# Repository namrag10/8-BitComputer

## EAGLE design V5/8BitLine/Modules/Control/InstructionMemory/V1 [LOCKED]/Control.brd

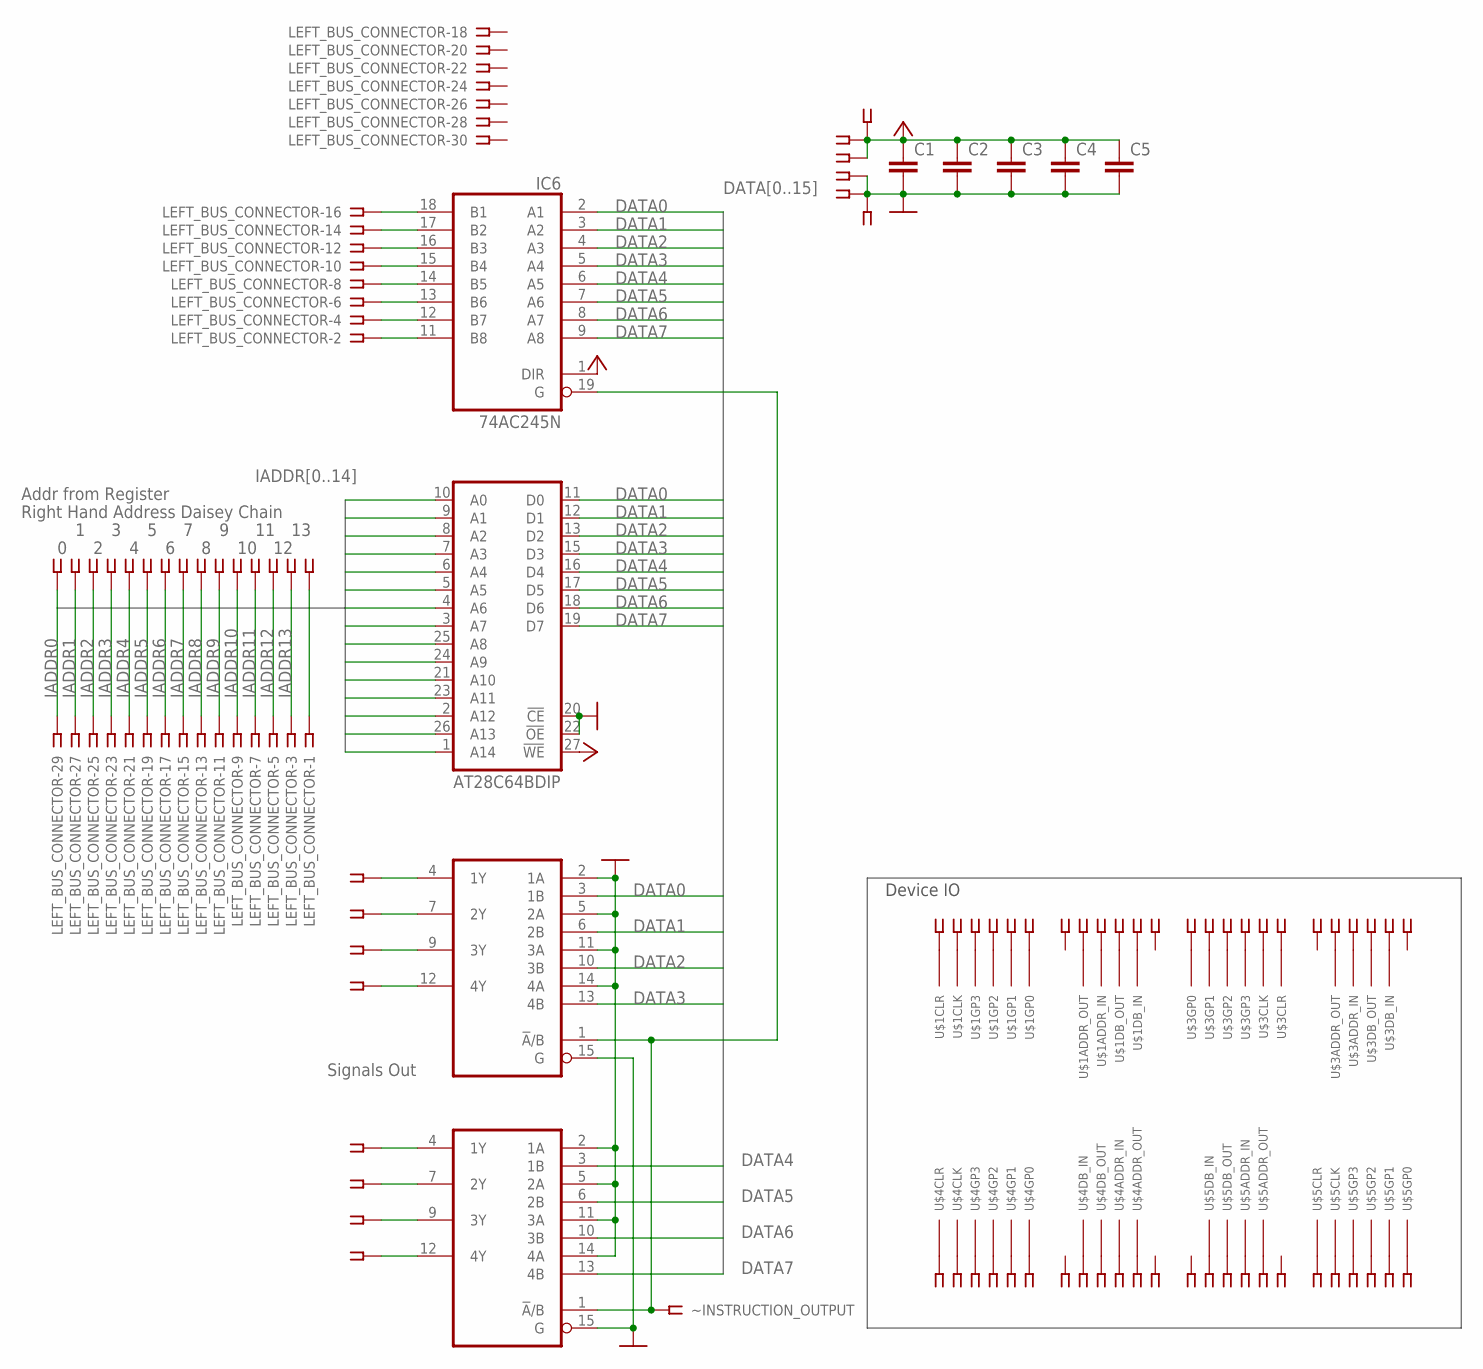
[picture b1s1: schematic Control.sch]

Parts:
C1, C2, C3, C4, C5: C2.5/2; C2.5-2
IC4, IC5: 74AC157N; DIL16
IC6: 74AC245N; DIL20
LEFT_BUS_CONNECTOR: SSW-115-02-G-D
MEZZANINE: SSW-104-02-G-S
U$1, U$3, U$4, U$5: CONTROL_SIG-INT; CONTROL_SIG-INT-FOOT
U$2: AT28C64BDIP; DIP28-WIDE
X1, X2, X3, X4, X6, X7, X8, X9: SSW-106-02-G-S
X5: SSW-108-02-G-S
X11: SSW-102-02-G-S
X12: SSW-115-02-G-S
~INSTRUCTION_OUTPUT: SSW-101-02-G-S

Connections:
DATA0: IC4.3 (1B), IC6.2 (A1), U$2.11 (D0)
DATA1: IC4.6 (2B), IC6.3 (A2), U$2.12 (D1)
DATA2: IC4.10 (3B), IC6.4 (A3), U$2.13 (D2)
DATA3: IC4.13 (4B), IC6.5 (A4), U$2.15 (D3)
DATA4: IC5.3 (1B), IC6.6 (A5), U$2.16 (D4)
DATA5: IC5.6 (2B), IC6.7 (A6), U$2.17 (D5)
DATA6: IC5.10 (3B), IC6.8 (A7), U$2.18 (D6)
DATA7: IC5.13 (4B), IC6.9 (A8), U$2.19 (D7)
GND: C1.2, C2.2, C3.2, C4.2, C5.2, IC4.2 (1A), IC4.5 (2A), IC4.8 (GND), IC4.11 (3A), IC4.14 (4A), IC4.15 (G), IC5.2 (1A), IC5.5 (2A), IC5.8 (GND), IC5.11 (3A), IC5.14 (4A), IC5.15 (G), IC6.10 (GND), MEZZANINE.3, MEZZANINE.4, U$1.GND, U$2.14 (GND), U$2.20 (!CE), U$2.22 (!OE), U$3.GND, U$4.GND, U$5.GND, X11.2
IADDR0: LEFT_BUS_CONNECTOR.29, U$2.10 (A0), X12.1
IADDR1: LEFT_BUS_CONNECTOR.27, U$2.9 (A1), X12.2
IADDR2: LEFT_BUS_CONNECTOR.25, U$2.8 (A2), X12.3
IADDR3: LEFT_BUS_CONNECTOR.23, U$2.7 (A3), X12.4
IADDR4: LEFT_BUS_CONNECTOR.21, U$2.6 (A4), X12.5
IADDR5: LEFT_BUS_CONNECTOR.19, U$2.5 (A5), X12.6
IADDR6: LEFT_BUS_CONNECTOR.17, U$2.4 (A6), X12.7
IADDR7: LEFT_BUS_CONNECTOR.15, U$2.3 (A7), X12.8
IADDR8: LEFT_BUS_CONNECTOR.13, U$2.25 (A8), X12.9
IADDR9: LEFT_BUS_CONNECTOR.11, U$2.24 (A9), X12.10
IADDR10: LEFT_BUS_CONNECTOR.9, U$2.21 (A10), X12.11
IADDR11: LEFT_BUS_CONNECTOR.7, U$2.23 (A11), X12.12
IADDR12: LEFT_BUS_CONNECTOR.5, U$2.2 (A12), X12.13
IADDR13: LEFT_BUS_CONNECTOR.3, U$2.26 (A13), X12.14
IADDR14: LEFT_BUS_CONNECTOR.1, U$2.1 (A14), X12.15
I_OUT: IC4.1 (!A!/B), IC5.1 (!A!/B), IC6.19 (G), ~INSTRUCTION_OUTPUT.1
unnamed: U$1.GP0 (0), X1.6
unnamed: U$1.GP1 (0), X1.5
unnamed: U$1.GP2 (0), X1.4
unnamed: U$1.GP3 (0), X1.3
unnamed: U$1.CLK (0), X1.2
unnamed: U$1.CLR (0), X1.1
unnamed: U$1.DB_IN (0), X2.2
unnamed: U$1.DB_OUT (0), X2.3
unnamed: U$1.ADDR_IN (0), X2.4
unnamed: U$1.ADDR_OT (0), X2.5
unnamed: U$3.GP0 (0), X3.6
unnamed: U$3.GP1 (0), X3.5
unnamed: U$3.GP2 (0), X3.4
unnamed: U$3.GP3 (0), X3.3
unnamed: U$3.CLK (0), X3.2
unnamed: U$3.CLR (0), X3.1
unnamed: U$3.DB_IN (0), X4.2
unnamed: U$3.DB_OUT (0), X4.3
unnamed: U$3.ADDR_IN (0), X4.4
unnamed: U$3.ADDR_OT (0), X4.5
unnamed: U$4.CLR (0), X9.1
unnamed: U$4.CLK (0), X9.2
unnamed: U$4.GP0 (0), X9.6
unnamed: U$4.GP1 (0), X9.5
unnamed: U$4.GP2 (0), X9.4
unnamed: U$4.GP3 (0), X9.3
unnamed: U$4.DB_IN (0), X8.2
unnamed: U$4.DB_OUT (0), X8.3
unnamed: U$4.ADDR_IN (0), X8.4
unnamed: U$4.ADDR_OT (0), X8.5
unnamed: U$5.GP0 (0), X6.6
unnamed: U$5.GP3 (0), X6.3
unnamed: U$5.GP2 (0), X6.4
unnamed: U$5.GP1 (0), X6.5
unnamed: U$5.CLK (0), X6.2
unnamed: U$5.CLR (0), X6.1
unnamed: U$5.DB_IN (0), X7.2
unnamed: U$5.DB_OUT (0), X7.3
unnamed: U$5.ADDR_IN (0), X7.4
unnamed: U$5.ADDR_OT (0), X7.5
O_DB0: IC6.18 (B1), LEFT_BUS_CONNECTOR.16
O_DB1: IC6.17 (B2), LEFT_BUS_CONNECTOR.14
O_DB2: IC6.16 (B3), LEFT_BUS_CONNECTOR.12
O_DB3: IC6.15 (B4), LEFT_BUS_CONNECTOR.10
O_DB4: IC6.14 (B5), LEFT_BUS_CONNECTOR.8
O_DB5: IC6.13 (B6), LEFT_BUS_CONNECTOR.6
O_DB6: IC6.12 (B7), LEFT_BUS_CONNECTOR.4
O_DB7: IC6.11 (B8), LEFT_BUS_CONNECTOR.2
SIG_1: IC4.4 (1Y), X5.1
SIG_2: IC4.7 (2Y), X5.2
SIG_3: IC4.9 (3Y), X5.3
SIG_4: IC4.12 (4Y), X5.4
SIG_5: IC5.4 (1Y), X5.5
SIG_6: IC5.7 (2Y), X5.6
SIG_7: IC5.9 (3Y), X5.7
SIG_8: IC5.12 (4Y), X5.8
VCC: C1.1, C2.1, C3.1, C4.1, C5.1, IC4.16 (VCC), IC5.16 (VCC), IC6.1 (DIR), IC6.20 (VCC), MEZZANINE.1, MEZZANINE.2, U$1.VCC, U$2.27 (!WE), U$2.28 (VCC), U$3.VCC, U$4.VCC, U$5.VCC, X11.1

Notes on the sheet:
Device IO
Signals Out
Right Hand Address Daisey Chain
Addr from Register

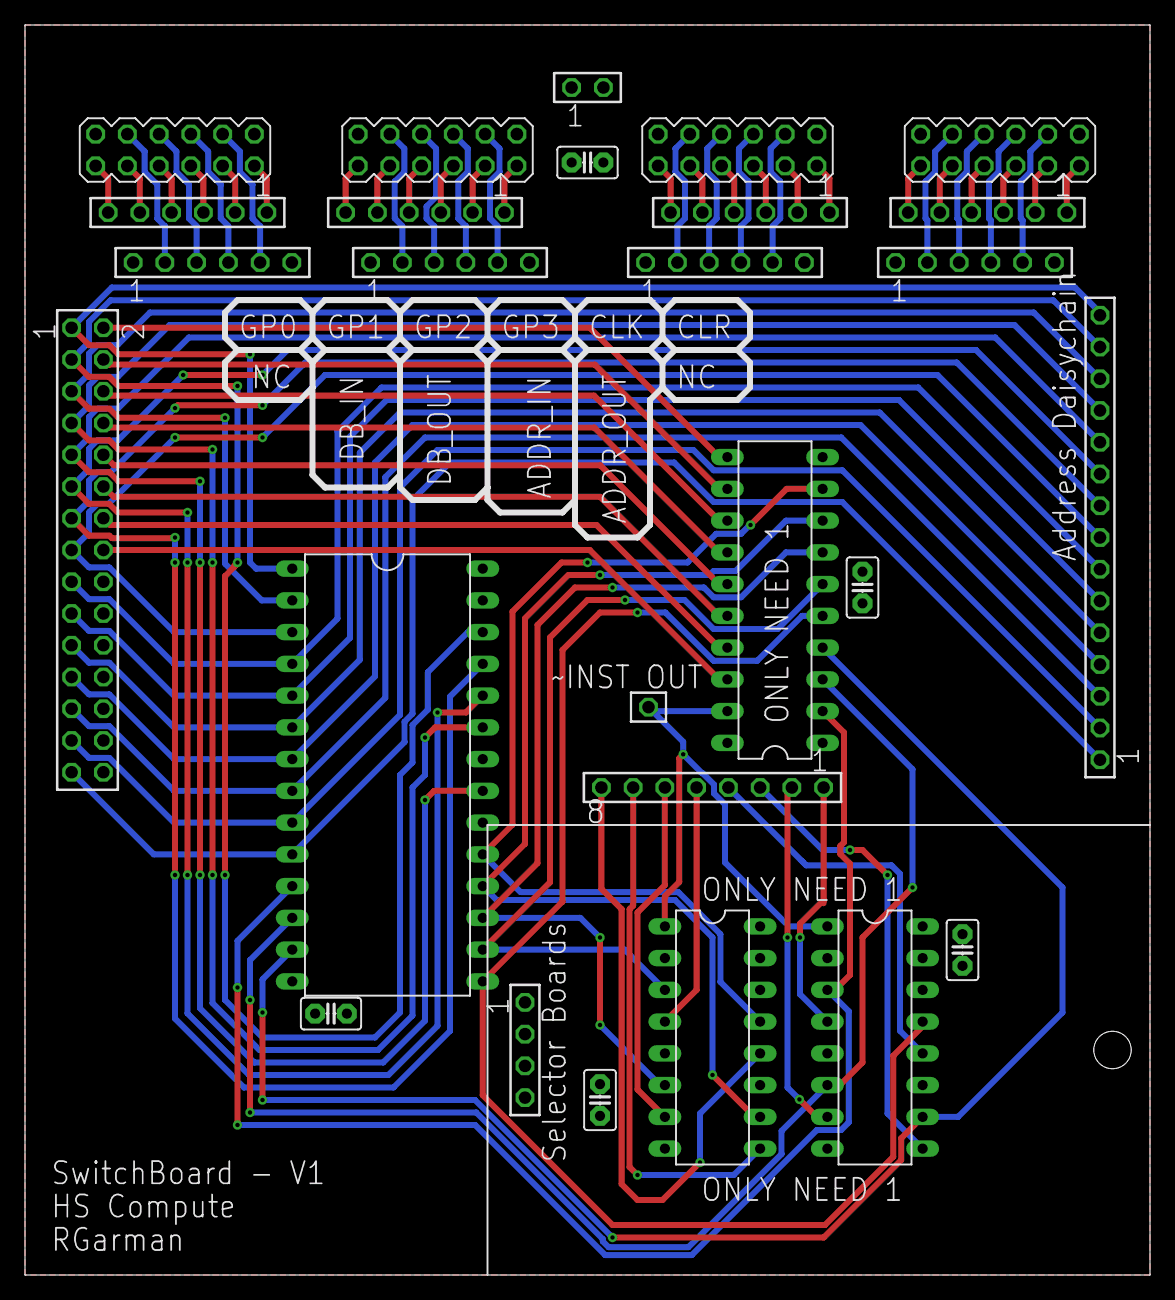
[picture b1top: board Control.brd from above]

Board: 2 copper layers, 90.0 x 100.0 mm, 27 parts (0 on the bottom side), 82 nets.

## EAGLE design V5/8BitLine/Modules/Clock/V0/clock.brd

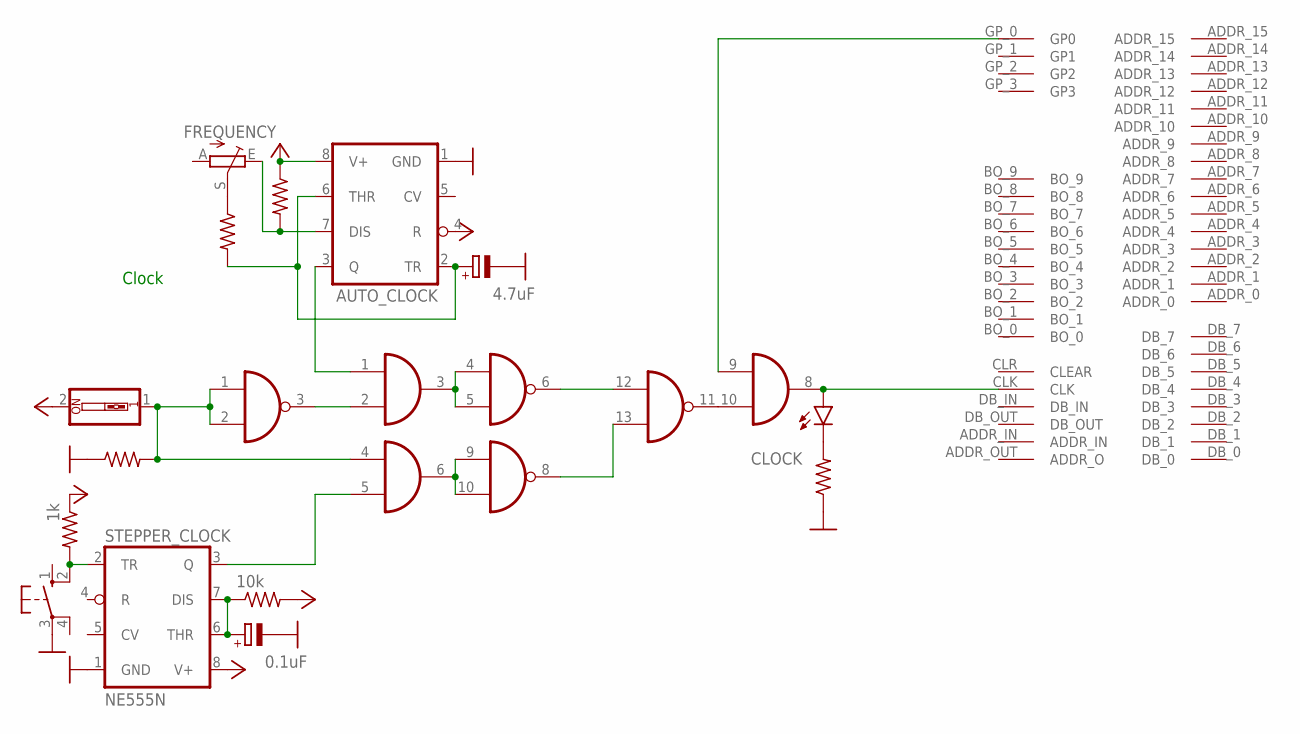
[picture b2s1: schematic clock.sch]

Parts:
AND_GATE_: 74LS08N; DIL14
AUTO_CLOCK: NE555N; DIL08
C1: 4.7uF; E2-5
C2: 0.1uF; E2-5
CLK_MODE: SWITCH; EDG-01
CLK_TRIGGER: SWITCH; B3F-10XX
CLOCK: Yellow; LED5MM
FREQUENCY: 100k; RJ9W
NAND: 74ACT00N; DIL14
R1, R2: 1k; 0204/7
R3: 10k; 0204/7
R4, R6: 220; 0204/7
R5: ~220; 0204/7
STEPPER_CLOCK: NE555N; DIL08
U$1: BACKPLATE_INTERFACEEDGE_FINGER; BACK_INTERFACE-FOOT

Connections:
CLOCK: AND_GATE_.8 (O), CLOCK.A, U$1.CLK
GND: AND_GATE_.7 (GND), AUTO_CLOCK.1 (GND), C1.-, C2.-, CLK_TRIGGER.3, NAND.7 (GND), R4.1, R5.1, STEPPER_CLOCK.1 (GND), U$1.GND_0 (GND), U$1.GND_1 (GND)
HLT: AND_GATE_.9 (I0), U$1.GP_0 (GP0)
MODE_SIGNAL: AND_GATE_.4 (I0), CLK_MODE.1, NAND.1 (I0), NAND.2 (I1), R4.2
unnamed: C2.+, R3.1, STEPPER_CLOCK.6 (THR), STEPPER_CLOCK.7 (DIS)
unnamed: CLK_TRIGGER.2 (S1), R2.2, STEPPER_CLOCK.2 (TR)
unnamed: CLOCK.K (C), R5.2
unnamed: AND_GATE_.5 (I1), STEPPER_CLOCK.3 (Q)
unnamed: AND_GATE_.3 (O), NAND.4 (I0), NAND.5 (I1)
unnamed: AND_GATE_.1 (I0), AUTO_CLOCK.3 (Q)
unnamed: AND_GATE_.6 (O), NAND.9 (I0), NAND.10 (I1)
unnamed: NAND.8 (O), NAND.13 (I1)
unnamed: AND_GATE_.2 (I1), NAND.3 (O)
unnamed: NAND.6 (O), NAND.12 (I0)
unnamed: AND_GATE_.10 (I1), NAND.11 (O)
unnamed: AUTO_CLOCK.2 (TR), AUTO_CLOCK.6 (THR), C1.+, R6.2
unnamed: FREQUENCY.S, R6.1
unnamed: AUTO_CLOCK.7 (DIS), FREQUENCY.E, R1.2
VCC: AND_GATE_.14 (VCC), AUTO_CLOCK.4 (R), AUTO_CLOCK.8 (V+), CLK_MODE.2, NAND.14 (VCC), R1.1, R2.1, R3.2, STEPPER_CLOCK.8 (V+), U$1.VCC_0 (VCC), U$1.VCC_1 (VCC)

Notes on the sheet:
Clock

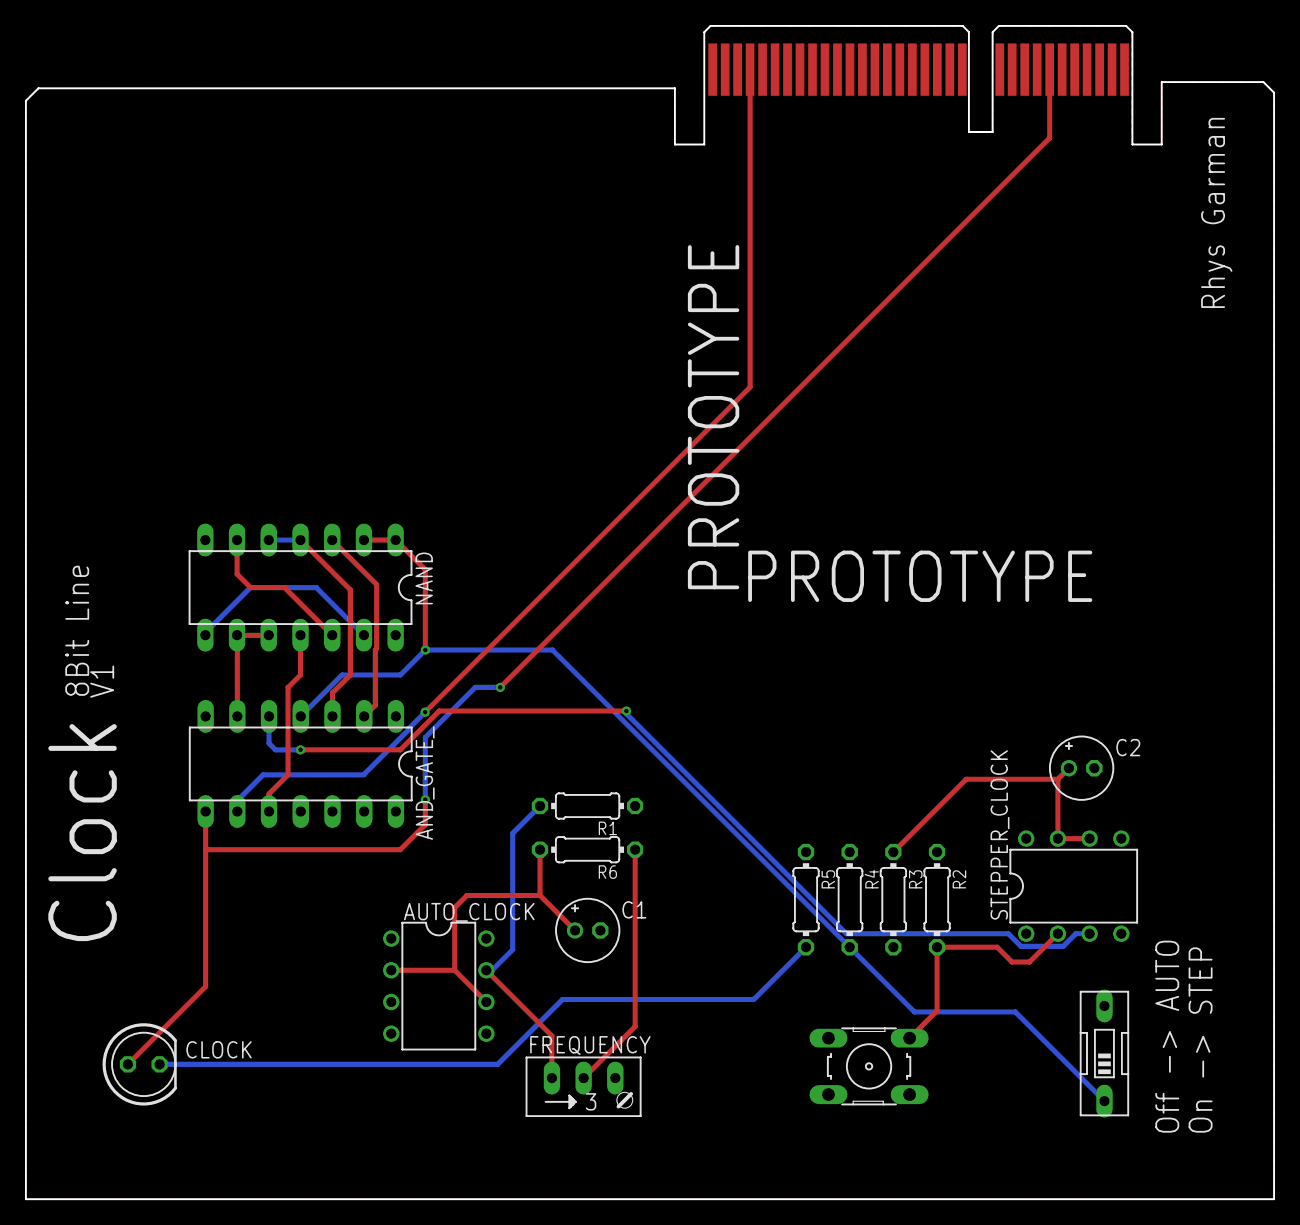
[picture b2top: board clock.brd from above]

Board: 2 copper layers, 100.0 x 94.0 mm, 17 parts (0 on the bottom side), 19 nets.

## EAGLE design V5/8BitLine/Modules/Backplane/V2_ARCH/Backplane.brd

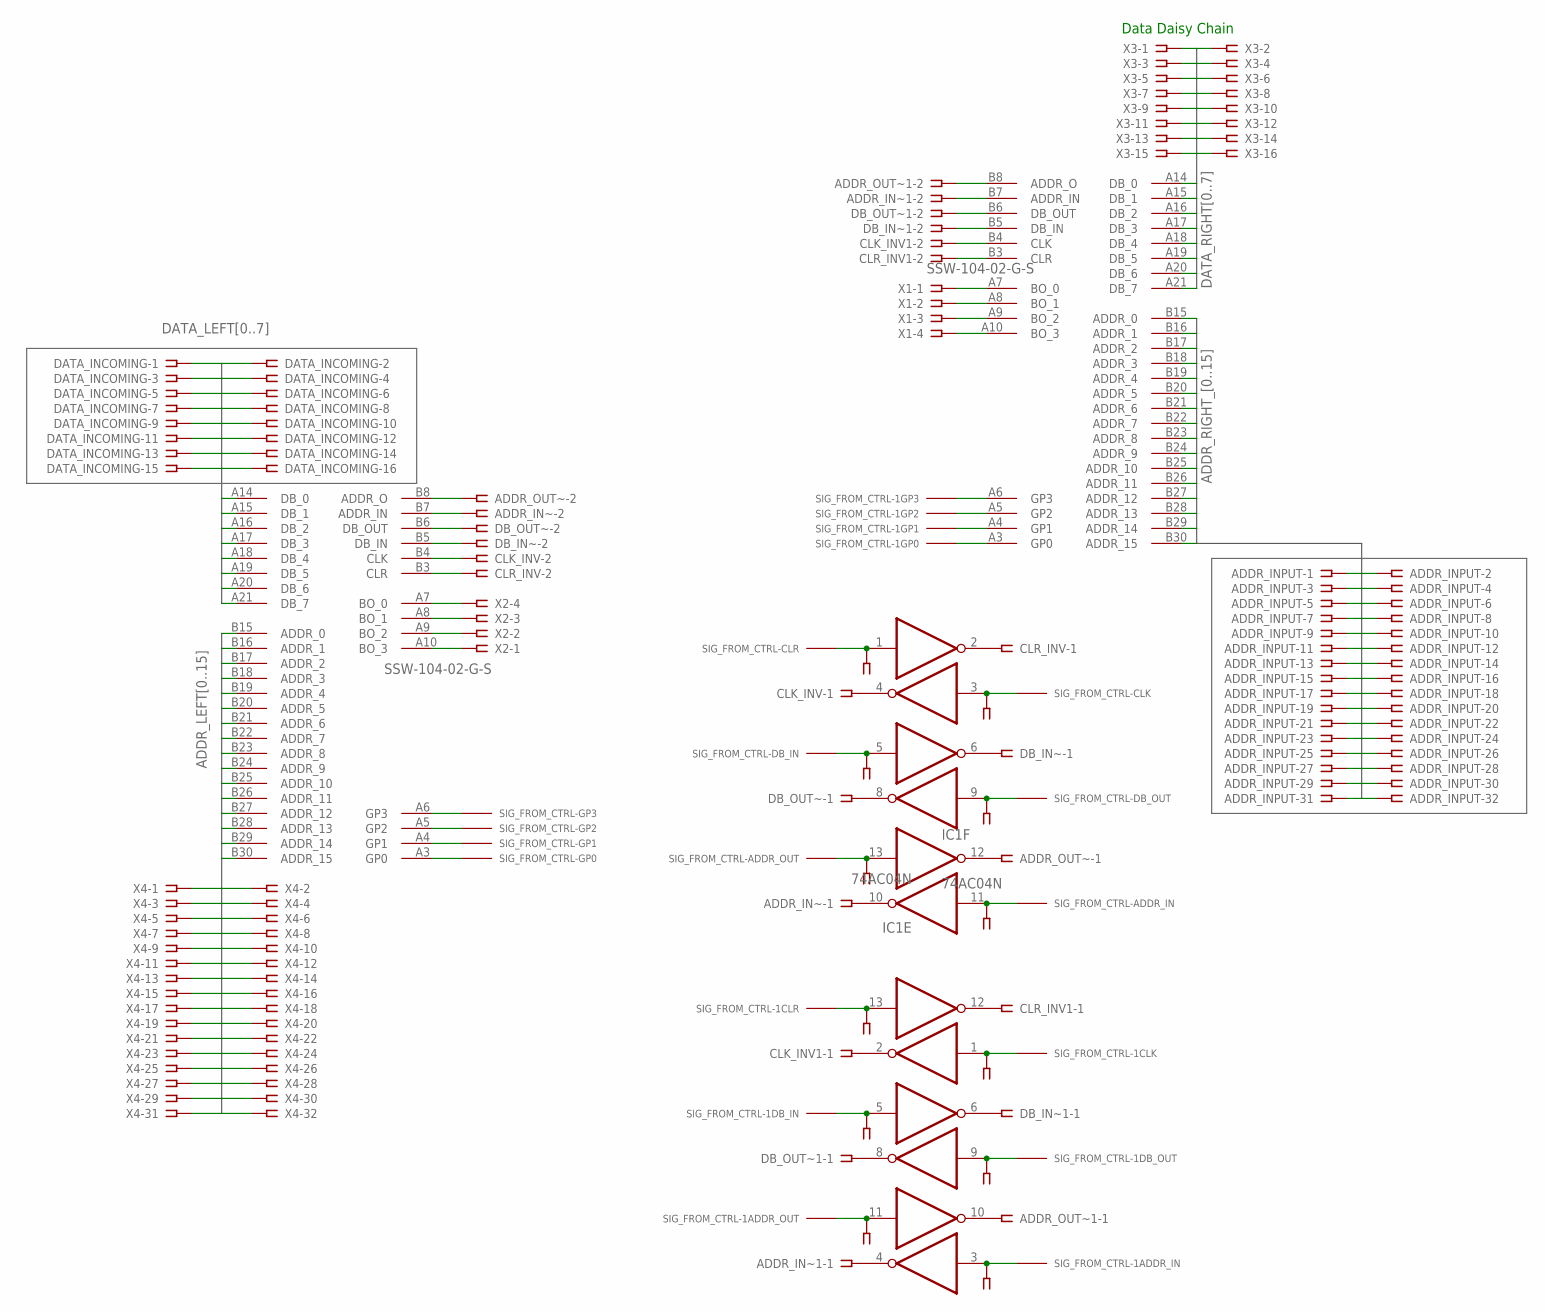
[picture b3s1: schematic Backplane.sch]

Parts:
ADDR_INPUT: SSW-116-02-G-D
ADDR_IN~, ADDR_IN~1: SSW-103-02-G-S
ADDR_OUT~, ADDR_OUT~1: SSW-103-02-G-S
CLK_INV, CLK_INV1: SSW-103-02-G-S
CLR_INV, CLR_INV1: SSW-103-02-G-S
DATA_INCOMING: SSW-108-02-G-D
DB_IN~, DB_IN~1: SSW-103-02-G-S
DB_OUT~, DB_OUT~1: SSW-103-02-G-S
IC1, IC2: 74AC04N; DIL14
SIG_FROM_CTRL-, SIG_FROM_CTRL-1: CONTROL_SIG-INT; CONTROL_SIG-INT-FOOT
U$1, U$2: BACKPLATE_INTERFACEHEADER; PCI_INTERFACE
X1, X2: SSW-104-02-G-S
X3: SSW-108-02-G-D
X4: SSW-116-02-G-D

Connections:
ADDR_IN: ADDR_IN~1.2, U$1.B7 (ADDR_IN)
ADDR_LEFT0: U$2.B15 (ADDR_0), X4.1, X4.2
ADDR_LEFT1: U$2.B16 (ADDR_1), X4.3, X4.4
ADDR_LEFT2: U$2.B17 (ADDR_2), X4.5, X4.6
ADDR_LEFT3: U$2.B18 (ADDR_3), X4.7, X4.8
ADDR_LEFT4: U$2.B19 (ADDR_4), X4.9, X4.10
ADDR_LEFT5: U$2.B20 (ADDR_5), X4.11, X4.12
ADDR_LEFT6: U$2.B21 (ADDR_6), X4.13, X4.14
ADDR_LEFT7: U$2.B22 (ADDR_7), X4.15, X4.16
ADDR_LEFT8: U$2.B23 (ADDR_8), X4.17, X4.18
ADDR_LEFT9: U$2.B24 (ADDR_9), X4.19, X4.20
ADDR_LEFT10: U$2.B25 (ADDR_10), X4.21, X4.22
ADDR_LEFT11: U$2.B26 (ADDR_11), X4.23, X4.24
ADDR_LEFT12: U$2.B27 (ADDR_12), X4.25, X4.26
ADDR_LEFT13: U$2.B28 (ADDR_13), X4.27, X4.28
ADDR_LEFT14: U$2.B29 (ADDR_14), X4.29, X4.30
ADDR_LEFT15: U$2.B30 (ADDR_15), X4.31, X4.32
ADDR_OUT: ADDR_OUT~1.2, U$1.B8 (ADDR_O)
ADDR_RIGHT_0: ADDR_INPUT.1, ADDR_INPUT.2, U$1.B15 (ADDR_0)
ADDR_RIGHT_1: ADDR_INPUT.3, ADDR_INPUT.4, U$1.B16 (ADDR_1)
ADDR_RIGHT_2: ADDR_INPUT.5, ADDR_INPUT.6, U$1.B17 (ADDR_2)
ADDR_RIGHT_3: ADDR_INPUT.7, ADDR_INPUT.8, U$1.B18 (ADDR_3)
ADDR_RIGHT_4: ADDR_INPUT.9, ADDR_INPUT.10, U$1.B19 (ADDR_4)
ADDR_RIGHT_5: ADDR_INPUT.11, ADDR_INPUT.12, U$1.B20 (ADDR_5)
ADDR_RIGHT_6: ADDR_INPUT.13, ADDR_INPUT.14, U$1.B21 (ADDR_6)
ADDR_RIGHT_7: ADDR_INPUT.15, ADDR_INPUT.16, U$1.B22 (ADDR_7)
ADDR_RIGHT_8: ADDR_INPUT.17, ADDR_INPUT.18, U$1.B23 (ADDR_8)
ADDR_RIGHT_9: ADDR_INPUT.19, ADDR_INPUT.20, U$1.B24 (ADDR_9)
ADDR_RIGHT_10: ADDR_INPUT.21, ADDR_INPUT.22, U$1.B25 (ADDR_10)
ADDR_RIGHT_11: ADDR_INPUT.23, ADDR_INPUT.24, U$1.B26 (ADDR_11)
ADDR_RIGHT_12: ADDR_INPUT.25, ADDR_INPUT.26, U$1.B27 (ADDR_12)
ADDR_RIGHT_13: ADDR_INPUT.27, ADDR_INPUT.28, U$1.B28 (ADDR_13)
ADDR_RIGHT_14: ADDR_INPUT.29, ADDR_INPUT.30, U$1.B29 (ADDR_14)
ADDR_RIGHT_15: ADDR_INPUT.31, ADDR_INPUT.32, U$1.B30 (ADDR_15)
BO_0: U$1.A7 (BO_0), X1.1
BO_1: U$1.A8 (BO_1), X1.2
BO_2: U$1.A9 (BO_2), X1.3
BO_3: U$1.A10 (BO_3), X1.4
CLK: CLK_INV1.2, U$1.B4 (CLK)
CLR: CLR_INV1.2, U$1.B3 (CLR)
DATA_LEFT0: DATA_INCOMING.1, DATA_INCOMING.2, U$2.A14 (DB_0)
DATA_LEFT1: DATA_INCOMING.3, DATA_INCOMING.4, U$2.A15 (DB_1)
DATA_LEFT2: DATA_INCOMING.5, DATA_INCOMING.6, U$2.A16 (DB_2)
DATA_LEFT3: DATA_INCOMING.7, DATA_INCOMING.8, U$2.A17 (DB_3)
DATA_LEFT4: DATA_INCOMING.9, DATA_INCOMING.10, U$2.A18 (DB_4)
DATA_LEFT5: DATA_INCOMING.11, DATA_INCOMING.12, U$2.A19 (DB_5)
DATA_LEFT6: DATA_INCOMING.13, DATA_INCOMING.14, U$2.A20 (DB_6)
DATA_LEFT7: DATA_INCOMING.15, DATA_INCOMING.16, U$2.A21 (DB_7)
DATA_RIGHT0: U$1.A14 (DB_0), X3.1, X3.2
DATA_RIGHT1: U$1.A15 (DB_1), X3.3, X3.4
DATA_RIGHT2: U$1.A16 (DB_2), X3.5, X3.6
DATA_RIGHT3: U$1.A17 (DB_3), X3.7, X3.8
DATA_RIGHT4: U$1.A18 (DB_4), X3.9, X3.10
DATA_RIGHT5: U$1.A19 (DB_5), X3.11, X3.12
DATA_RIGHT6: U$1.A20 (DB_6), X3.13, X3.14
DATA_RIGHT7: U$1.A21 (DB_7), X3.15, X3.16
DB_IN: DB_IN~1.2, U$1.B5 (DB_IN)
DB_OUT: DB_OUT~1.2, U$1.B6 (DB_OUT)
GND: IC1.7 (GND), IC2.7 (GND), SIG_FROM_CTRL-.GND, SIG_FROM_CTRL-1.GND, U$1.B2 (GND), U$1.B31 (GND), U$2.B2 (GND), U$2.B31 (GND)
GP0: SIG_FROM_CTRL-1.GP0 (0), U$1.A3 (GP0)
GP1: SIG_FROM_CTRL-1.GP1 (0), U$1.A4 (GP1)
GP2: SIG_FROM_CTRL-1.GP2 (0), U$1.A5 (GP2)
GP3: SIG_FROM_CTRL-1.GP3 (0), U$1.A6 (GP3)
unnamed: CLR_INV.2, U$2.B3 (CLR)
unnamed: CLR_INV.3, IC1.1 (I), SIG_FROM_CTRL-.CLR (0)
unnamed: CLK_INV.2, U$2.B4 (CLK)
unnamed: DB_IN~.2, U$2.B5 (DB_IN)
unnamed: DB_OUT~.2, U$2.B6 (DB_OUT)
unnamed: SIG_FROM_CTRL-.GP0 (0), U$2.A3 (GP0)
unnamed: SIG_FROM_CTRL-.GP1 (0), U$2.A4 (GP1)
unnamed: CLK_INV.3, IC1.3 (I), SIG_FROM_CTRL-.CLK (0)
unnamed: DB_IN~.3, IC1.5 (I), SIG_FROM_CTRL-.DB_IN (0)
unnamed: DB_OUT~.3, IC1.9 (I), SIG_FROM_CTRL-.DB_OUT (0)
unnamed: SIG_FROM_CTRL-.GP2 (0), U$2.A5 (GP2)
unnamed: SIG_FROM_CTRL-.GP3 (0), U$2.A6 (GP3)
unnamed: ADDR_OUT~.3, IC1.13 (I), SIG_FROM_CTRL-.ADDR_OT (0)
unnamed: ADDR_IN~.1, IC1.10 (O)
unnamed: CLR_INV.1, IC1.2 (O)
unnamed: CLK_INV.1, IC1.4 (O)
unnamed: DB_IN~.1, IC1.6 (O)
unnamed: DB_OUT~.1, IC1.8 (O)
unnamed: ADDR_IN~.3, IC1.11 (I), SIG_FROM_CTRL-.ADDR_IN (0)
unnamed: ADDR_OUT~.1, IC1.12 (O)
unnamed: ADDR_OUT~.2, U$2.B8 (ADDR_O)
unnamed: ADDR_IN~.2, U$2.B7 (ADDR_IN)
unnamed: U$2.A10 (BO_3), X2.1
unnamed: U$2.A9 (BO_2), X2.2
unnamed: U$2.A8 (BO_1), X2.3
unnamed: U$2.A7 (BO_0), X2.4
unnamed: CLR_INV1.3, IC2.13 (I), SIG_FROM_CTRL-1.CLR (0)
unnamed: CLK_INV1.3, IC2.1 (I), SIG_FROM_CTRL-1.CLK (0)
unnamed: DB_IN~1.3, IC2.5 (I), SIG_FROM_CTRL-1.DB_IN (0)
unnamed: DB_OUT~1.3, IC2.9 (I), SIG_FROM_CTRL-1.DB_OUT (0)
unnamed: CLK_INV1.1, IC2.2 (O)
unnamed: ADDR_IN~1.1, IC2.4 (O)
unnamed: DB_IN~1.1, IC2.6 (O)
unnamed: DB_OUT~1.1, IC2.8 (O)
unnamed: ADDR_OUT~1.3, IC2.11 (I), SIG_FROM_CTRL-1.ADDR_OT (0)
unnamed: ADDR_IN~1.3, IC2.3 (I), SIG_FROM_CTRL-1.ADDR_IN (0)
unnamed: ADDR_OUT~1.1, IC2.10 (O)
unnamed: CLR_INV1.1, IC2.12 (O)
VCC: IC1.14 (VCC), IC2.14 (VCC), SIG_FROM_CTRL-.VCC, SIG_FROM_CTRL-1.VCC, U$1.A2 (VCC), U$1.A31 (VCC), U$2.A2 (VCC), U$2.A31 (VCC)

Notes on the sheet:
Data Daisy Chain

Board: 2 copper layers, 24 parts (0 on the bottom side), 102 nets, no tracks yet.

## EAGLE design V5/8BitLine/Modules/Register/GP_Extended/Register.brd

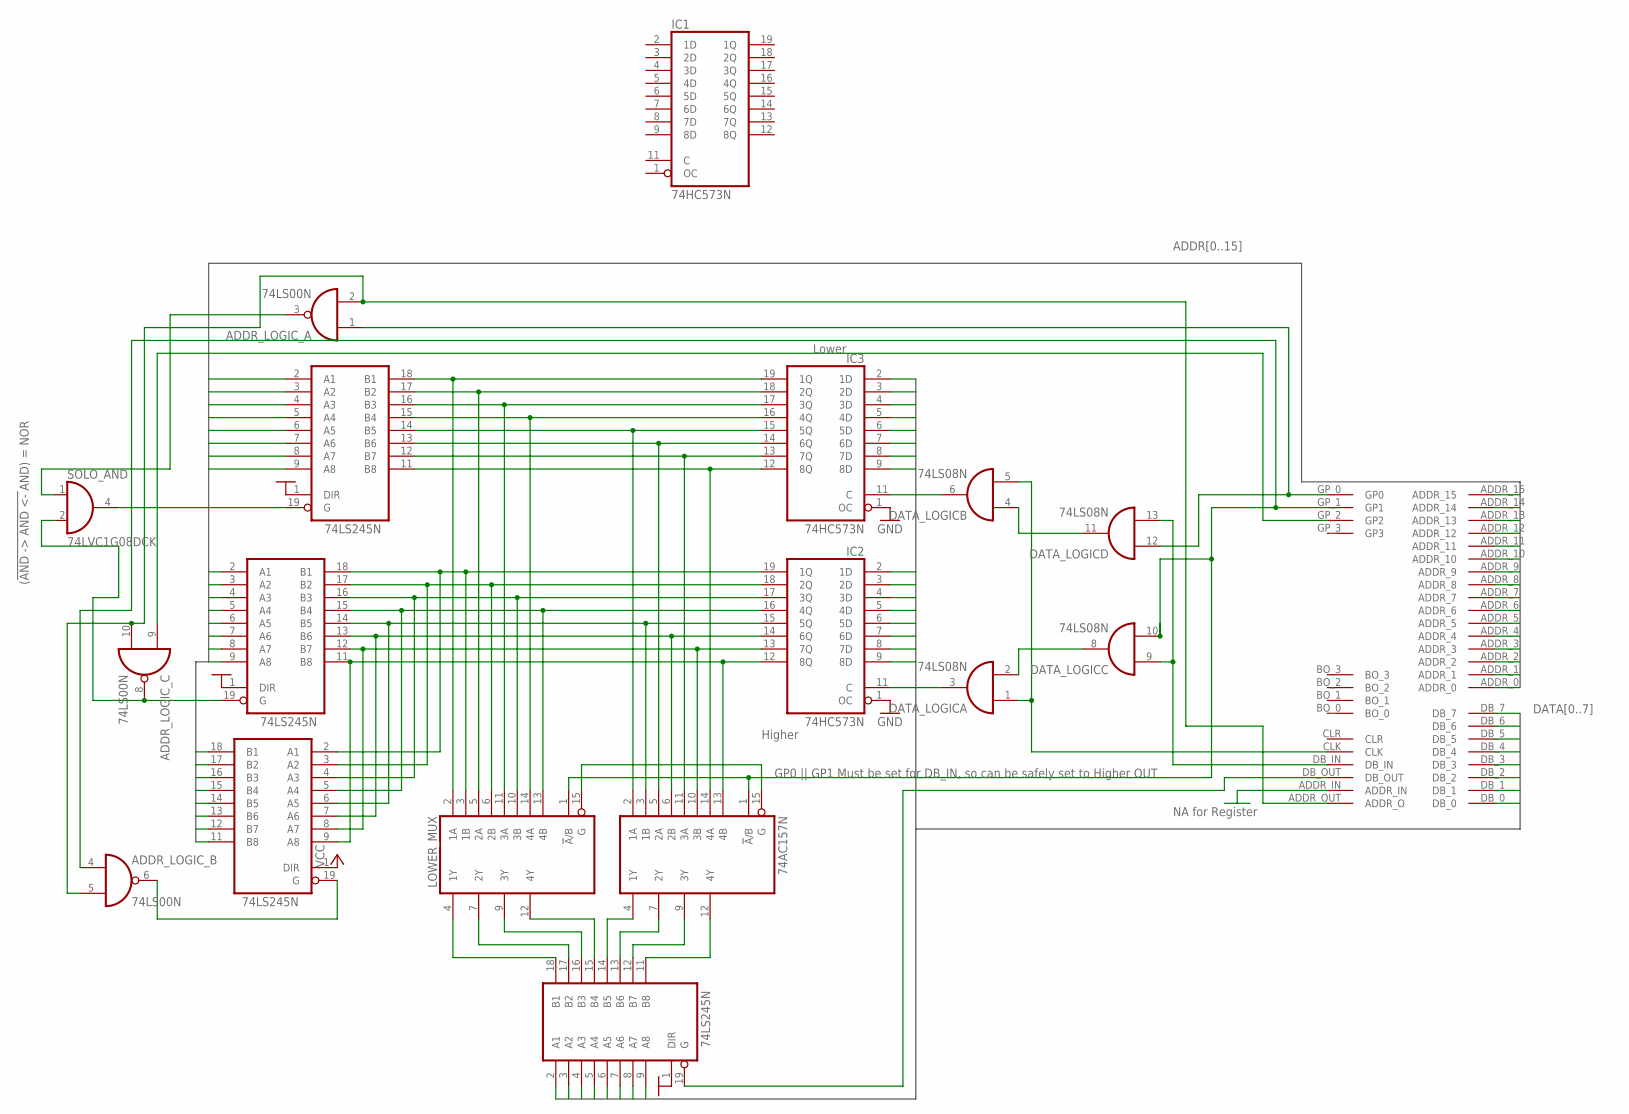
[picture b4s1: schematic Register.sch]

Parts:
ADDR_HIGHER_BUFFER: 74LS245N; DIL20
ADDR_HIGHER_TO_LOWER: 74LS245N; DIL20
ADDR_LOGIC_: 74LS00N; DIL14
ADDR_LOWER_BUFFER: 74LS245N; DIL20
DATA_LOGIC: 74LS08N; DIL14
DATA_OUTPUT_BUFFER: 74LS245N; DIL20
HIGHER_MUX: 74AC157N; DIL16
IC1, IC2, IC3: 74HC573N; DIL20
LOWER_MUX: 74AC157N; DIL16
SOLO_AND: 74LVC1G08DCK; SC70-5
U$1: BACKPLATE_INTERFACEEDGE_FINGER; BACK_INTERFACE-FOOT

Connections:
ADDR0: ADDR_HIGHER_TO_LOWER.18 (B1), ADDR_LOWER_BUFFER.2 (A1), U$1.ADDR_0
ADDR1: ADDR_HIGHER_TO_LOWER.17 (B2), ADDR_LOWER_BUFFER.3 (A2), U$1.ADDR_1
ADDR2: ADDR_HIGHER_TO_LOWER.16 (B3), ADDR_LOWER_BUFFER.4 (A3), U$1.ADDR_2
ADDR3: ADDR_HIGHER_TO_LOWER.15 (B4), ADDR_LOWER_BUFFER.5 (A4), U$1.ADDR_3
ADDR4: ADDR_HIGHER_TO_LOWER.14 (B5), ADDR_LOWER_BUFFER.6 (A5), U$1.ADDR_4
ADDR5: ADDR_HIGHER_TO_LOWER.13 (B6), ADDR_LOWER_BUFFER.7 (A6), U$1.ADDR_5
ADDR6: ADDR_HIGHER_TO_LOWER.12 (B7), ADDR_LOWER_BUFFER.8 (A7), U$1.ADDR_6
ADDR7: ADDR_HIGHER_TO_LOWER.11 (B8), ADDR_LOWER_BUFFER.9 (A8), U$1.ADDR_7
ADDR8: ADDR_HIGHER_BUFFER.2 (A1), U$1.ADDR_8
ADDR9: ADDR_HIGHER_BUFFER.3 (A2), U$1.ADDR_9
ADDR10: ADDR_HIGHER_BUFFER.4 (A3), U$1.ADDR_10
ADDR11: ADDR_HIGHER_BUFFER.5 (A4), U$1.ADDR_11
ADDR12: ADDR_HIGHER_BUFFER.6 (A5), U$1.ADDR_12
ADDR13: ADDR_HIGHER_BUFFER.7 (A6), U$1.ADDR_13
ADDR14: ADDR_HIGHER_BUFFER.8 (A7), U$1.ADDR_14
ADDR15: ADDR_HIGHER_BUFFER.9 (A8), U$1.ADDR_15
CLK: DATA_LOGIC.1 (I0), DATA_LOGIC.5 (I1), U$1.CLK
CTRL_ADDR_OUT: ADDR_LOGIC_.2 (I1), ADDR_LOGIC_.5 (I1), ADDR_LOGIC_.10 (I1), U$1.ADDR_OUT (ADDR_O)
CTRL_DB_IN: DATA_LOGIC.9 (I0), DATA_LOGIC.13 (I1), U$1.DB_IN
CTRL_DB_OUT: DATA_OUTPUT_BUFFER.19 (G), U$1.DB_OUT
DATA0: DATA_OUTPUT_BUFFER.2 (A1), IC2.2 (1D), IC3.2 (1D), U$1.DB_0
DATA1: DATA_OUTPUT_BUFFER.3 (A2), IC2.3 (2D), IC3.3 (2D), U$1.DB_1
DATA2: DATA_OUTPUT_BUFFER.4 (A3), IC2.4 (3D), IC3.4 (3D), U$1.DB_2
DATA3: DATA_OUTPUT_BUFFER.5 (A4), IC2.5 (4D), IC3.5 (4D), U$1.DB_3
DATA4: DATA_OUTPUT_BUFFER.6 (A5), IC2.6 (5D), IC3.6 (5D), U$1.DB_4
DATA5: DATA_OUTPUT_BUFFER.7 (A6), IC2.7 (6D), IC3.7 (6D), U$1.DB_5
DATA6: DATA_OUTPUT_BUFFER.8 (A7), IC2.8 (7D), IC3.8 (7D), U$1.DB_6
DATA7: DATA_OUTPUT_BUFFER.9 (A8), IC2.9 (8D), IC3.9 (8D), U$1.DB_7
DATA_0: ADDR_LOWER_BUFFER.18 (B1), IC3.19 (1Q), LOWER_MUX.2 (1A)
DATA_1: ADDR_LOWER_BUFFER.17 (B2), IC3.18 (2Q), LOWER_MUX.5 (2A)
DATA_2: ADDR_LOWER_BUFFER.16 (B3), IC3.17 (3Q), LOWER_MUX.11 (3A)
DATA_3: ADDR_LOWER_BUFFER.15 (B4), IC3.16 (4Q), LOWER_MUX.14 (4A)
DATA_4: ADDR_LOWER_BUFFER.14 (B5), HIGHER_MUX.2 (1A), IC3.15 (5Q)
DATA_5: ADDR_LOWER_BUFFER.13 (B6), HIGHER_MUX.5 (2A), IC3.14 (6Q)
DATA_6: ADDR_LOWER_BUFFER.12 (B7), HIGHER_MUX.11 (3A), IC3.13 (7Q)
DATA_7: ADDR_LOWER_BUFFER.11 (B8), HIGHER_MUX.14 (4A), IC3.12 (8Q)
DATA_8: ADDR_HIGHER_BUFFER.18 (B1), ADDR_HIGHER_TO_LOWER.2 (A1), IC2.19 (1Q), LOWER_MUX.3 (1B)
DATA_9: ADDR_HIGHER_BUFFER.17 (B2), ADDR_HIGHER_TO_LOWER.3 (A2), IC2.18 (2Q), LOWER_MUX.6 (2B)
DATA_10: ADDR_HIGHER_BUFFER.16 (B3), ADDR_HIGHER_TO_LOWER.4 (A3), IC2.17 (3Q), LOWER_MUX.10 (3B)
DATA_11: ADDR_HIGHER_BUFFER.15 (B4), ADDR_HIGHER_TO_LOWER.5 (A4), IC2.16 (4Q), LOWER_MUX.13 (4B)
DATA_12: ADDR_HIGHER_BUFFER.14 (B5), ADDR_HIGHER_TO_LOWER.6 (A5), HIGHER_MUX.3 (1B), IC2.15 (5Q)
DATA_13: ADDR_HIGHER_BUFFER.13 (B6), ADDR_HIGHER_TO_LOWER.7 (A6), HIGHER_MUX.6 (2B), IC2.14 (6Q)
DATA_14: ADDR_HIGHER_BUFFER.12 (B7), ADDR_HIGHER_TO_LOWER.8 (A7), HIGHER_MUX.10 (3B), IC2.13 (7Q)
DATA_15: ADDR_HIGHER_BUFFER.11 (B8), ADDR_HIGHER_TO_LOWER.9 (A8), HIGHER_MUX.13 (4B), IC2.12 (8Q)
GND: ADDR_HIGHER_BUFFER.1 (DIR), ADDR_HIGHER_BUFFER.10 (GND), ADDR_HIGHER_TO_LOWER.10 (GND), ADDR_LOGIC_.7 (GND), ADDR_LOWER_BUFFER.1 (DIR), ADDR_LOWER_BUFFER.10 (GND), DATA_LOGIC.7 (GND), DATA_OUTPUT_BUFFER.1 (DIR), DATA_OUTPUT_BUFFER.10 (GND), HIGHER_MUX.8 (GND), IC1.10 (GND), IC2.1 (OC), IC2.10 (GND), IC3.1 (OC), IC3.10 (GND), LOWER_MUX.8 (GND), SOLO_AND.3 (GND), U$1.GND_0 (GND), U$1.GND_1 (GND)
GP_0: ADDR_LOGIC_.1 (I0), DATA_LOGIC.12 (I0), U$1.GP_0 (GP0)
GP_1: ADDR_LOGIC_.4 (I0), DATA_LOGIC.10 (I1), HIGHER_MUX.1 (!A!/B), LOWER_MUX.1 (!A!/B), U$1.GP_1 (GP1)
GP_2: ADDR_LOGIC_.9 (I0), U$1.GP_2 (GP2)
unnamed: DATA_OUTPUT_BUFFER.18 (B1), LOWER_MUX.4 (1Y)
unnamed: DATA_OUTPUT_BUFFER.17 (B2), LOWER_MUX.7 (2Y)
unnamed: DATA_LOGIC.6 (O), IC3.11 (C)
unnamed: DATA_LOGIC.3 (O), IC2.11 (C)
unnamed: DATA_LOGIC.4 (I0), DATA_LOGIC.11 (O)
unnamed: DATA_LOGIC.2 (I1), DATA_LOGIC.8 (O)
unnamed: DATA_OUTPUT_BUFFER.16 (B3), LOWER_MUX.9 (3Y)
unnamed: DATA_OUTPUT_BUFFER.15 (B4), LOWER_MUX.12 (4Y)
unnamed: DATA_OUTPUT_BUFFER.14 (B5), HIGHER_MUX.4 (1Y)
unnamed: DATA_OUTPUT_BUFFER.13 (B6), HIGHER_MUX.7 (2Y)
unnamed: DATA_OUTPUT_BUFFER.12 (B7), HIGHER_MUX.9 (3Y)
unnamed: DATA_OUTPUT_BUFFER.11 (B8), HIGHER_MUX.12 (4Y)
unnamed: ADDR_HIGHER_TO_LOWER.19 (G), ADDR_LOGIC_.6 (O)
unnamed: HIGHER_MUX.15 (G), LOWER_MUX.15 (G)
unnamed: ADDR_HIGHER_BUFFER.19 (G), ADDR_LOGIC_.8 (O), SOLO_AND.2 (I1)
unnamed: ADDR_LOGIC_.3 (O), SOLO_AND.1 (I0)
unnamed: ADDR_LOWER_BUFFER.19 (G), SOLO_AND.4 (O)
VCC: ADDR_HIGHER_BUFFER.20 (VCC), ADDR_HIGHER_TO_LOWER.1 (DIR), ADDR_HIGHER_TO_LOWER.20 (VCC), ADDR_LOGIC_.14 (VCC), ADDR_LOWER_BUFFER.20 (VCC), DATA_LOGIC.14 (VCC), DATA_OUTPUT_BUFFER.20 (VCC), HIGHER_MUX.16 (VCC), IC1.20 (VCC), IC2.20 (VCC), IC3.20 (VCC), LOWER_MUX.16 (VCC), SOLO_AND.5 (VCC), U$1.VCC_0 (VCC), U$1.VCC_1 (VCC)

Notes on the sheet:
Lower
Higher
GP0 || GP1 Must be set for DB_IN, so can be safely set to Higher OUT
NA for Register
(!AND -> AND <- !AND) = NOR

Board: 4 copper layers, 13 parts (0 on the bottom side), 66 nets, no tracks yet.

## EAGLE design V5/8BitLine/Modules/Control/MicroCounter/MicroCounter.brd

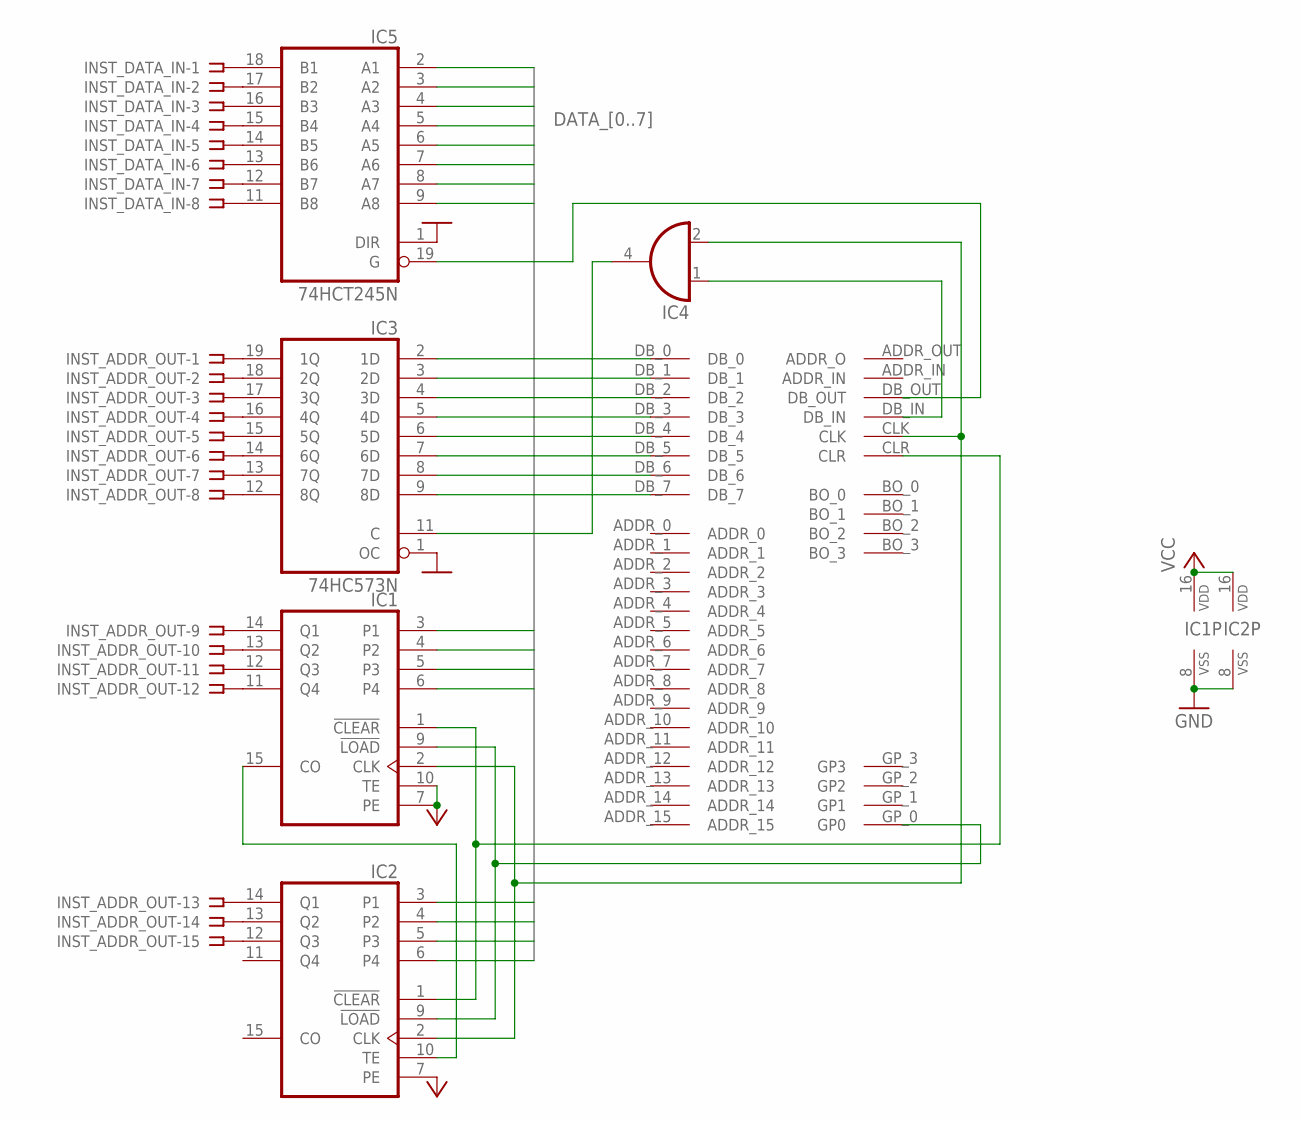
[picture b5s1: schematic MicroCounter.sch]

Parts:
IC1, IC2: 4161N; DIL16
IC3: 74HC573N; DIL20
IC4: 74LVC1G08DCK; SC70-5
IC5: 74HCT245N; DIL20
INST_ADDR_OUT: SSW-115-02-G-S
INST_DATA_IN: SSW-108-02-G-S
U$1: BACKPLATE_INTERFACEEDGE_FINGER; BACK_INTERFACE-FOOT

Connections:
DATA_0: IC1.3 (P1), IC3.2 (1D), IC5.2 (A1), U$1.DB_0
DATA_1: IC1.4 (P2), IC3.3 (2D), IC5.3 (A2), U$1.DB_1
DATA_2: IC1.5 (P3), IC3.4 (3D), IC5.4 (A3), U$1.DB_2
DATA_3: IC1.6 (P4), IC3.5 (4D), IC5.5 (A4), U$1.DB_3
DATA_4: IC2.3 (P1), IC3.6 (5D), IC5.6 (A5), U$1.DB_4
DATA_5: IC2.4 (P2), IC3.7 (6D), IC5.7 (A6), U$1.DB_5
DATA_6: IC2.5 (P3), IC3.8 (7D), IC5.8 (A7), U$1.DB_6
DATA_7: IC2.6 (P4), IC3.9 (8D), IC5.9 (A8), U$1.DB_7
GND: IC1.8 (VSS), IC2.8 (VSS), IC3.1 (OC), IC3.10 (GND), IC4.3 (GND), IC5.1 (DIR), IC5.10 (GND), U$1.GND_0 (GND), U$1.GND_1 (GND)
unnamed: IC3.19 (1Q), INST_ADDR_OUT.1
unnamed: IC5.18 (B1), INST_DATA_IN.1
unnamed: IC5.17 (B2), INST_DATA_IN.2
unnamed: IC5.16 (B3), INST_DATA_IN.3
unnamed: IC5.15 (B4), INST_DATA_IN.4
unnamed: IC3.18 (2Q), INST_ADDR_OUT.2
unnamed: IC5.14 (B5), INST_DATA_IN.5
unnamed: IC5.13 (B6), INST_DATA_IN.6
unnamed: IC5.12 (B7), INST_DATA_IN.7
unnamed: IC5.11 (B8), INST_DATA_IN.8
unnamed: IC3.17 (3Q), INST_ADDR_OUT.3
unnamed: IC3.16 (4Q), INST_ADDR_OUT.4
unnamed: IC3.15 (5Q), INST_ADDR_OUT.5
unnamed: IC3.14 (6Q), INST_ADDR_OUT.6
unnamed: IC3.13 (7Q), INST_ADDR_OUT.7
unnamed: IC3.12 (8Q), INST_ADDR_OUT.8
unnamed: IC1.14 (Q1), INST_ADDR_OUT.9
unnamed: IC1.13 (Q2), INST_ADDR_OUT.10
unnamed: IC1.12 (Q3), INST_ADDR_OUT.11
unnamed: IC1.11 (Q4), INST_ADDR_OUT.12
unnamed: IC2.14 (Q1), INST_ADDR_OUT.13
unnamed: IC2.13 (Q2), INST_ADDR_OUT.14
unnamed: IC2.12 (Q3), INST_ADDR_OUT.15
unnamed: IC3.11 (C), IC4.4 (O)
unnamed: IC1.15 (CO), IC2.10 (TE)
unnamed: IC4.1 (I0), U$1.DB_IN
unnamed: IC5.19 (G), U$1.DB_OUT
unnamed: IC1.1 (!CLEAR), IC2.1 (!CLEAR), U$1.CLR
unnamed: IC1.2 (CLK), IC2.2 (CLK), IC4.2 (I1), U$1.CLK
SUB_LOAD: IC1.9 (!LOAD), IC2.9 (!LOAD), U$1.GP_0 (GP0)
VCC: IC1.7 (PE), IC1.10 (TE), IC1.16 (VDD), IC2.7 (PE), IC2.16 (VDD), IC3.20 (VCC), IC4.5 (VCC), IC5.20 (VCC), U$1.VCC_0 (VCC), U$1.VCC_1 (VCC)
